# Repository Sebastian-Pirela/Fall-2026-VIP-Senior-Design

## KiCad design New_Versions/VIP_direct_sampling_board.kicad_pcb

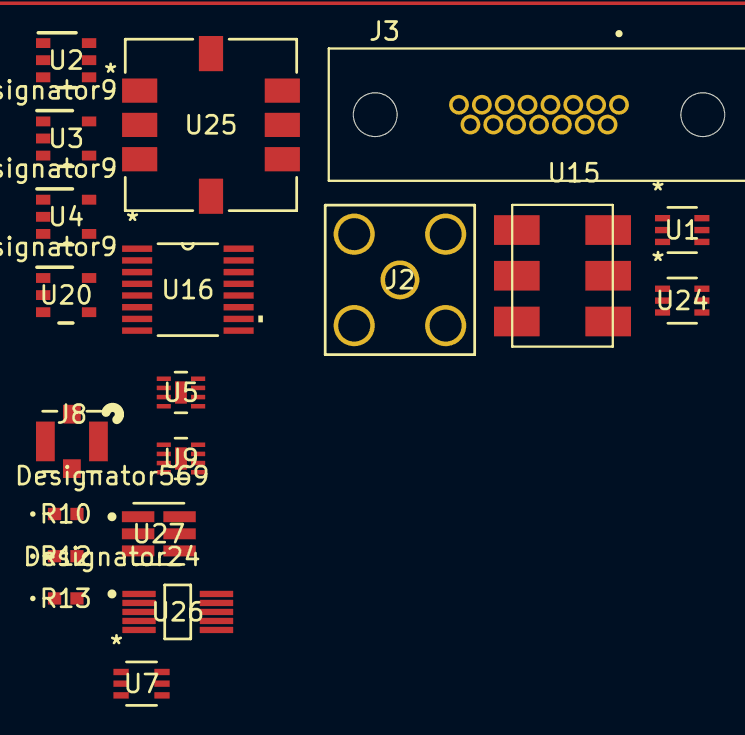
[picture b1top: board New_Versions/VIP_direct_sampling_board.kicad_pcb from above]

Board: 2 copper layers, 20 parts (0 on the bottom side), 19 nets, no tracks yet.

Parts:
J2: 142-0701-201; ul_142-0701-201
J3: 380-015-213L001
J8: CONMHF1-SMD-G-T; ul_CONMHF1-SMD-G-T
R10, R12, R13: FC0402E50R0BST1; ul_FC0402E50R0BST1
U1, U24: PSA-8A+; ul_PSA-8A-
U2: TPS22918TDBVRQ1; ul_TPS22918TDBVRQ1
U3, U4, U20: LP5907MFX-3.0/NOPB; ul_LP5907MFX-3-0-NOPB
U5, U9: TSS-23ULN+; ul_TSS-23ULN- (1)
U7: LM66100DCKR; ul_LM66100DCKR
U15: ADC-20-4_
U16: ADS7830IPWR; ul_ADS7830IPWR
U25: RBP-140+; ul_RBP-140- (1)
U26: TMUX1104DGSR; ul_TMUX1104DGSR (1)
U27: TPS22810TDBVRQ1; ul_TPS22810TDBVRQ1

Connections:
3V0_RF: U4.5 (VOUT), U5.6 (VSHUTDOWN), U9.6 (VSHUTDOWN), U26.6 (VDD)
5V_DIODE: U7.3 (*CE), U7.6 (VOUT)
5V_F: U2.1 (VIN), U3.1 (VIN), U3.3 (EN)
5V_SW: U2.5 (QOD), U2.6 (VOUT), U4.1 (VIN), U4.3 (EN), U20.1 (VIN)
+5V: J3.2, U7.1 (VIN), U26.5 (EN)
CAL_CTRL_S0: J3.6, U27.3 (EN_UVLO)
CAL_CTRL_S1: J3.5, U26.10 (A1)
CAL_CTRL_S2: J3.4, U26.1 (A0)
COLD_LNA_EN: J3.12, U20.3 (EN)
GND: J3.3, J8.2 (GND), J8.3 (GND), J8.4 (GND), R10.1, R12.1, R13.1, U1.1 (GND), U1.2 (GND), U1.4 (GND), U1.5 (GND), U2.2 (GND), U3.2 (GND), U4.2 (GND), U5.9 (GND), U7.2 (GND), U7.5 (ST), U9.9 (GND), U15.2, U16.8 (CH7), U16.9 (GND), U16.11 (COM), U16.12 (A0), U16.13 (A1), U20.2 (GND), U24.1 (GND), U24.2 (GND), U24.4 (GND), U24.5 (GND), U25.1 (GROUND), U25.3 (GROUND), U25.4 (GROUND), U25.5 (GROUND), U25.7 (GROUND), U25.8 (GROUND), U26.3 (GND), U26.7 (S4), U27.2 (GND)
I2C_DSA_SCL: J3.10, U16.14 (SCL)
I2C_SDA: J3.9, U16.15 (SDA)
unnamed: R12.2, U15.4
unnamed: U25.6 (OUTPUT), U26.2 (S1)
unnamed: U15.1, U26.8 (D)
unnamed: R10.2, U26.9 (S2)
unnamed: U5.2 (RF-IN), U26.4 (S3)
RF_IN: J2.1, U25.2 (INPUT)
RF_INTERMEDIATE: U9.2 (RF-IN), U15.6

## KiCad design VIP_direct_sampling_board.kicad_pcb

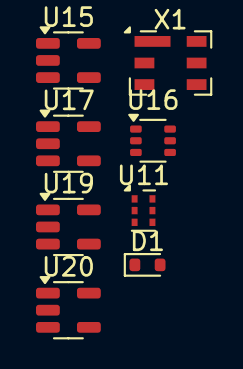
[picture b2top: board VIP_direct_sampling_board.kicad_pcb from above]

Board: 2 copper layers, 8 parts (0 on the bottom side), 4 nets, no tracks yet.

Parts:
D1: GC6002-350A; D_SOD-523
U11: DC4759J5020AHF-1; Anaren_0805_2012Metric-6
U15, U17, U20: LP5907MFX-3.0; SOT-23-5
U16: LM66100DCK; SOT-363_SC-70-6
U19: LP5907MFX-4.5; SOT-23-5
X1: B3715; Filter_SAW_Epcos_DCC6C_3x3mm

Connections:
5V_Diode: U16.3 (~CE), U16.6 (VOUT), U17.1 (IN), U17.3 (EN)
5V_F: U15.1 (IN), U19.1 (IN), U19.3 (EN), U20.1 (IN), U20.3 (EN)
GND: U11.3 (GND), U11.4 (GND), U15.2 (GND), U16.2 (GND), U16.5 (ST), U17.2 (GND), U19.2 (GND), U20.2 (GND), X1.1 (GND), X1.3 (GND), X1.4 (GND), X1.6 (GND)
unnamed: D1.1 (K), U11.2 (Isolated)
